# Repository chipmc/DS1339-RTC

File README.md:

# DS1339 RTC
DS1339 Real Time Clock Module
 
Created with EAGLE v9 - Information here including a free version - https://www.autodesk.com/products/eagle/overview

If you simply want to order this board, here is an OSHPark link: https://oshpark.com/shared_projects/rNxANV7V
 
This is a basic implementation of the Maxim DS1339 Real Time Clock.  The I2C and Interrupt pins are all presented on a 6-pin header.  There is also a 2-pin header to allow for other sources of battery backup power should you not chose to use the CR1225 coin cell on the back.

This is open source hardware, please feel free to use and improve according to the attached license.  This hardware was developed by See Insights LLC for a project sponsored by Jay Ham, Colorado State University - Thank You!

# Related Software Projects

The original library by Shridhar Rajagopal - https://github.com/sridharrajagopal/DSRTCLib

An adaptation of Shridhar's project I made for the Particle platform - https://github.com/chipmc/RTC-Watchdog

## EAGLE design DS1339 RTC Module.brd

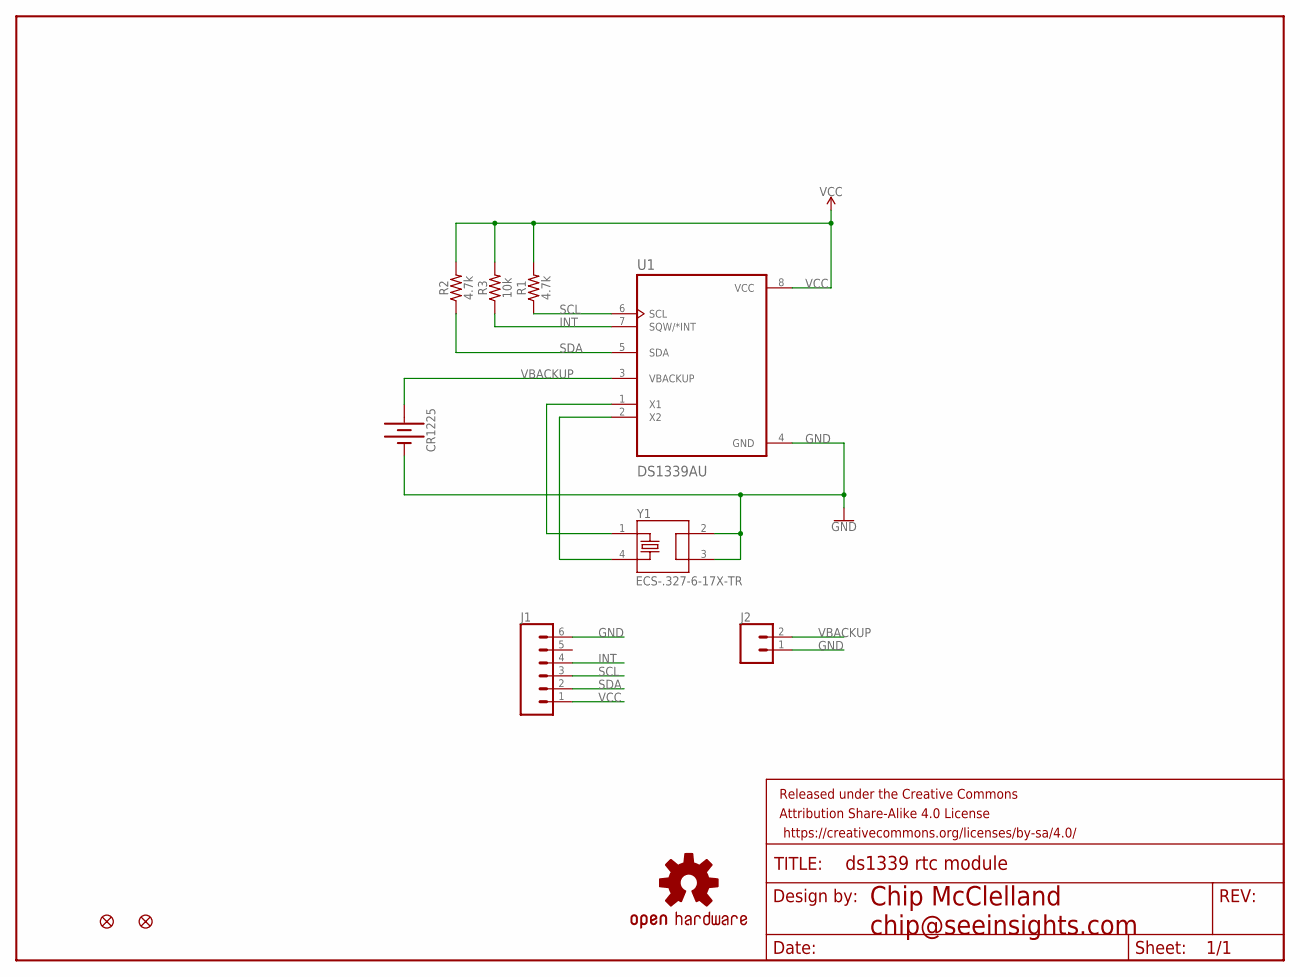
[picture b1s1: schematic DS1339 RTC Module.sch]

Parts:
CR1225: BATTERY-12MM_SMD; BATTCON_12MM
FD1, FD2: FIDUCIALUFIDUCIAL; FIDUCIAL-MICRO
FRAME1: FRAME-LETTER; CREATIVE_COMMONS
J1: CONN_06LOCK; 1X06_LOCK
J2: CONN_02; 1X02
LOGO1: OSHW-LOGOMINI; OSHW-LOGO-MINI
R1, R2: 4.7k; 0805
R3: 10k; 0805
U1: DS1339AU; SOP65P490X110-8N
Y1: ECS-.327-6-17X-TR; XTAL_ECS-.327-6-17X-TR

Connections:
GND: CR1225.GND (-), J1.6, J2.1, U1.4 (GND), Y1.2, Y1.3
INT: J1.4, R3.1, U1.7 (SQW/*INT)
unnamed: U1.1 (X1), Y1.1
unnamed: U1.2 (X2), Y1.4
SCL: J1.3, R1.1, U1.6 (SCL)
SDA: J1.2, R2.1, U1.5 (SDA)
VBACKUP: CR1225.PWR@2 (+), J2.2, U1.3 (VBACKUP)
VCC: J1.1, R1.2, R2.2, R3.2, U1.8 (VCC)

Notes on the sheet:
Chip McClelland chip@seeinsights.com

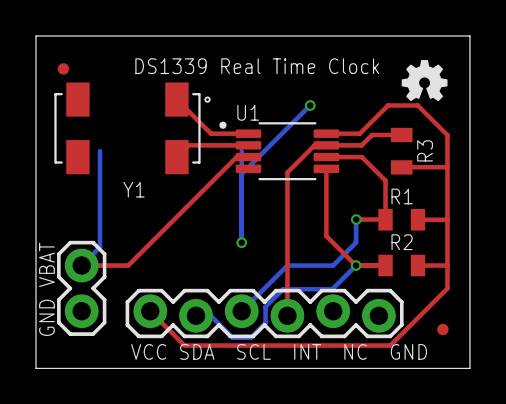
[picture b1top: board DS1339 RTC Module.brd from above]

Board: 2 copper layers, 24.1 x 18.5 mm, 12 parts (1 on the bottom side), 8 nets.

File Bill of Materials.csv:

Part,Value,Device,Package,Digikey,Description,DESCRIPTION,DIGI-KEY_PART_NUMBER,DIGI-KEY_PURCHASE_URL,MF,MP,PACKAGE,PROD_ID,SF_SKU,VALUE,
CR1225,,BATTERY-12MM_SMD,BATTCON_12MM,EBR1225-ND,Battery - Single Cell,,,,,,,BATT-08044,PRT-10592,,
J1,,CONN_06LOCK,1X06_LOCK,,Multi connection point. Often used as Generic Header-pin footprint for 0.1 inch spaced/style header connections,,,,,,,,,,
J2,,CONN_02,1X02,,Multi connection point. Often used as Generic Header-pin footprint for 0.1 inch spaced/style header connections,,,,,,,,,,
R1,4.7k,RESISTOR0805,0805,311-4.70KCRCT-ND,Generic Resistor Package,,,,,,, ,, ,
R2,4.7k,RESISTOR0805,0805,311-4.70KCRCT-ND,Generic Resistor Package,,,,,,, ,, ,
R3,10k,RESISTOR0805,0805,311-10.0KCRCT-ND,Generic Resistor Package,,,,,,, ,, ,
U1,DS1339AU,DS1339AU,SOP65P490X110-8N,DS1339U-33+T&RCT-ND,,Real Time Clock Serial 8-Pin uMAX,DS1339AU+-ND,https://www.digikey.com/product-detail/en/maxim-integrated/D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,Maxim Integrated,DS1339AU+,&amp,MICRO,MAX-8 Maxim,,
Y1,ECS-.327-6-17X-TR,ECS-.327-6-17X-TR,XTAL_ECS-.327-6-17X-TR,XC1307CT-ND,"Crystal  4-SOJ, 5.50mm pitch",ECX-306X Series 32.768 kHz ±20 ppm 6 pF -40 to +85 °C SMT Tuning Fork Crystal,XC1307CT-ND,https://www.digikey.com/product-detail/en/ecs-inc/ECS-.327-6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,ECS Inc.,ECS-.327-6-17X-TR,4-4 ECS International,,,,

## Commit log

2019-08-22 Updated for Publishing
2019-08-22 Aesthetic Updates
2019-08-22 Oops - Flipped VCC and GND on connector
2019-08-22 Fine Tuned some routing
2019-08-22 Added labels on the bottom too.
2019-08-22 Added BOM and values
2019-08-22 Rename DS1339 RTC Module.csv to Bill of Materials.csv
2019-08-29 Updated with links to the Software libs

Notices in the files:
parts and their libraries:
SparkFun-Aesthetics: Licensing: Creative Commons ShareAlike 4.0 International - https://creativecommons.org/licenses/by-sa/4.0
SparkFun-Aesthetics: Released under the Creative Commons Attribution Share-Alike 4.0 License
SparkFun-Aesthetics: https://creativecommons.org/licenses/by-sa/4.0
